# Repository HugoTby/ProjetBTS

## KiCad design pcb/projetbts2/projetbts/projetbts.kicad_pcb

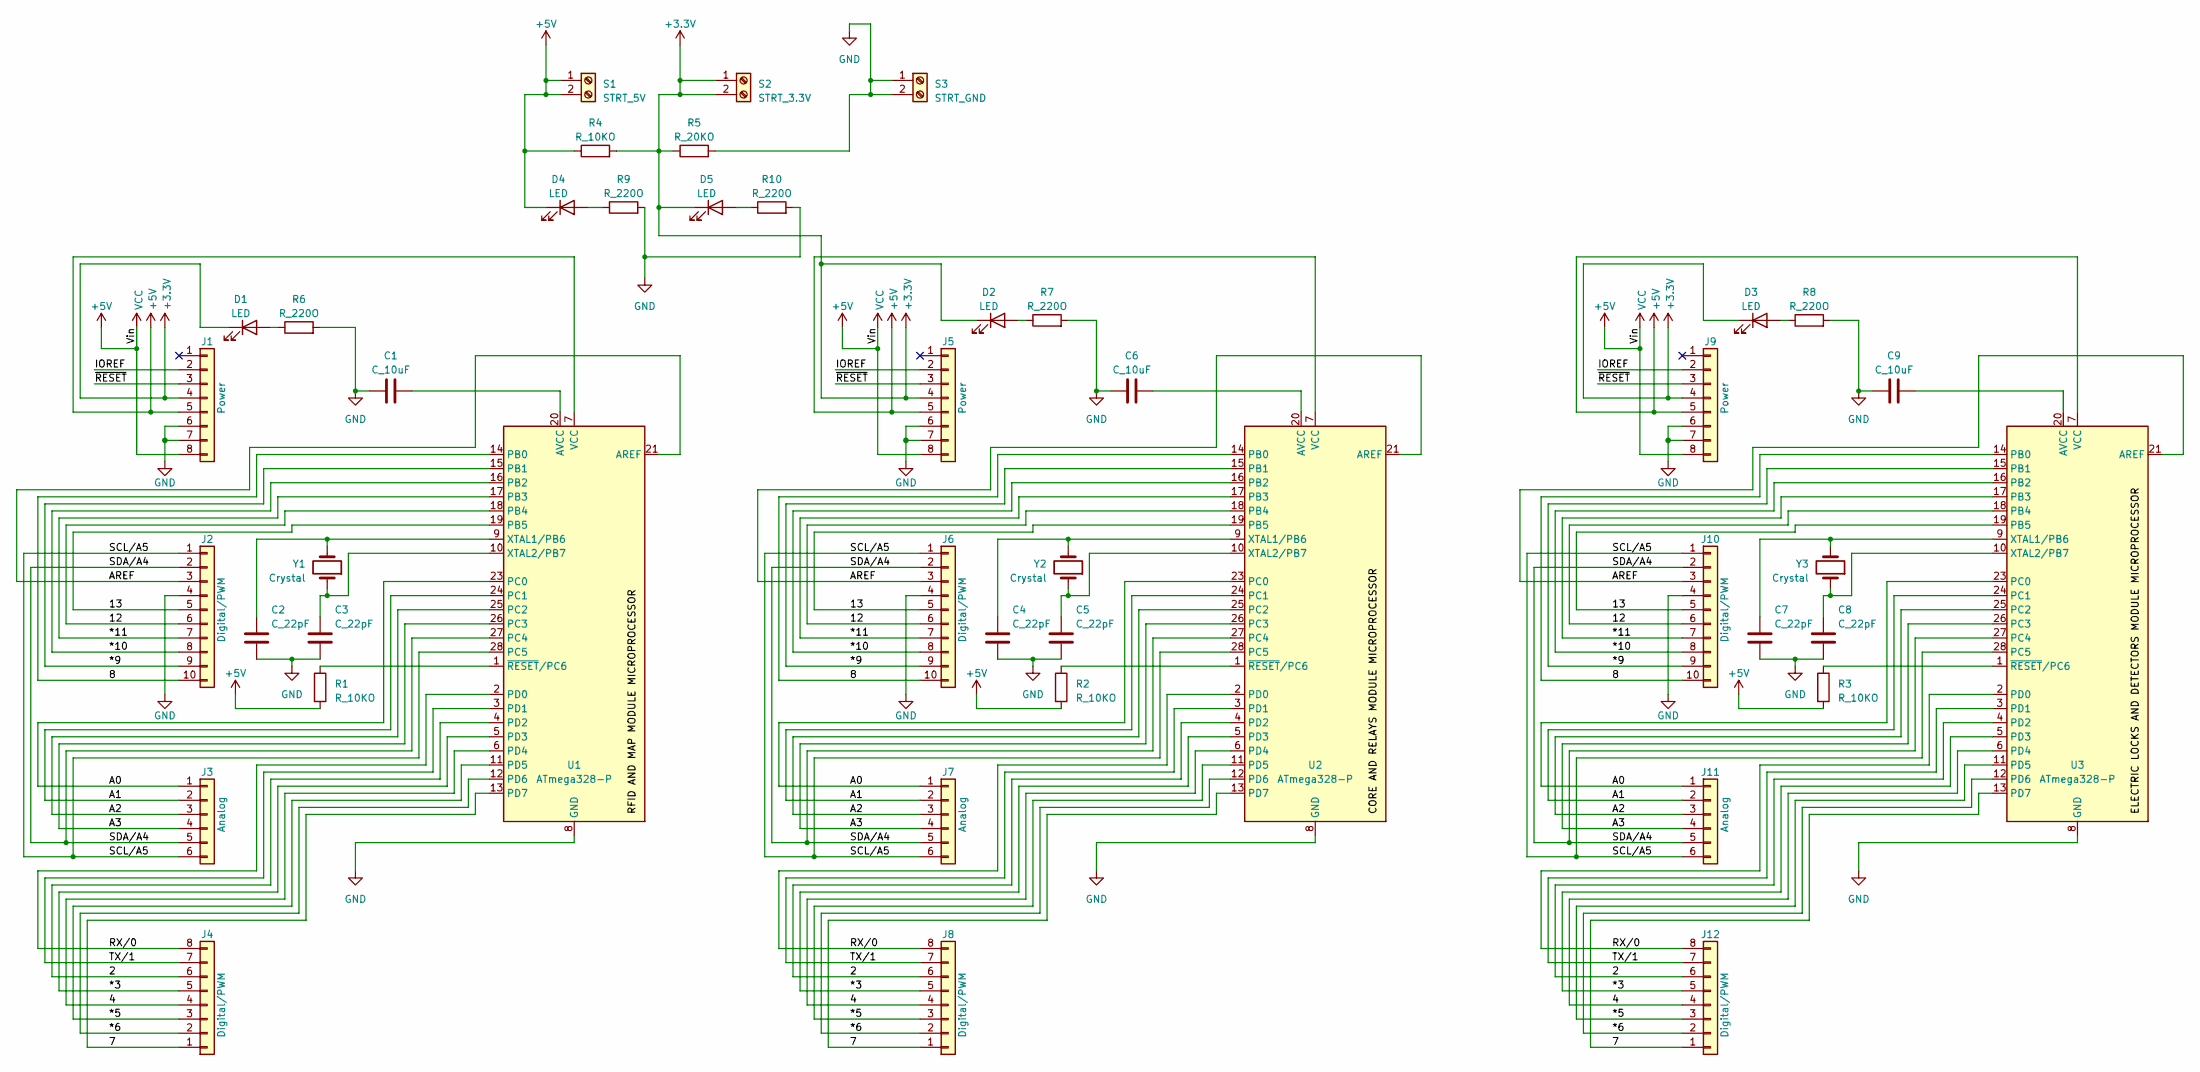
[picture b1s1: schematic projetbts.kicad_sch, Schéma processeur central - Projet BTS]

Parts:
C1, C6, C9: C_10uF; C_Disc_D7.5mm_W5.0mm_P5.00mm
C2, C3, C4, C5, C7, C8: C_22pF; C_Disc_D7.5mm_W5.0mm_P5.00mm
D1, D2, D3, D4, D5: LED; LED_D3.0mm
J1, J5, J9: Power; PinSocket_1x08_P2.54mm_Vertical
J2, J6, J10: Digital/PWM; PinSocket_1x10_P2.54mm_Vertical
J3, J7, J11: Analog; PinSocket_1x06_P2.54mm_Vertical
J4, J8, J12: Digital/PWM; PinSocket_1x08_P2.54mm_Vertical
R1, R2, R3, R4: R_10KO; R_Axial_DIN0207_L6.3mm_D2.5mm_P7.62mm_Horizontal
R5: R_20KO; R_Axial_DIN0207_L6.3mm_D2.5mm_P7.62mm_Horizontal
R6, R7, R8, R9, R10: R_220O; R_Axial_DIN0207_L6.3mm_D2.5mm_P7.62mm_Horizontal
S1: STRT_5V; TerminalBlock_bornier-2_P5.08mm
S2: STRT_3.3V; TerminalBlock_bornier-2_P5.08mm
S3: STRT_GND; TerminalBlock_bornier-2_P5.08mm
U1, U2, U3: ATmega328-P; DIP-28_W7.62mm
Y1, Y2, Y3: Crystal; Crystal_HC49-4H_Vertical

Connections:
+3.3V: D1.1 (K), D2.1 (K), D3.1 (K), D5.1 (K), J1.4, J5.4, J9.4, R4.2, R5.1, S2.1, S2.2; also elsewhere on the board
+5V: D4.1 (K), J1.5, J1.8, J5.5, J5.8, J9.5, J9.8, R1.2, R2.2, R3.2, R4.1, S1.1, S1.2, U1.7 (VCC), U2.7 (VCC), U3.7 (VCC); also elsewhere on the board
/2: J4.6, J8.6, J12.6, U1.4 (PD2), U2.4 (PD2), U3.4 (PD2)
/4: J4.4, J8.4, J12.4, U1.6 (PD4), U2.6 (PD4), U3.6 (PD4)
/7: J4.1, J8.1, J12.1, U1.13 (PD7), U2.13 (PD7), U3.13 (PD7)
/8: J2.10, J6.10, J10.10, U1.14 (PB0), U2.14 (PB0), U3.14 (PB0)
/12: J2.6, J6.6, J10.6, U1.18 (PB4), U2.18 (PB4), U3.18 (PB4)
/13: J2.5, J6.5, J10.5, U1.19 (PB5), U2.19 (PB5), U3.19 (PB5)
/*3: J4.5, J8.5, J12.5, U1.5 (PD3), U2.5 (PD3), U3.5 (PD3)
/*5: J4.3, J8.3, J12.3, U1.11 (PD5), U2.11 (PD5), U3.11 (PD5)
/*6: J4.2, J8.2, J12.2, U1.12 (PD6), U2.12 (PD6), U3.12 (PD6)
/*9: J2.9, J6.9, J10.9, U1.15 (PB1), U2.15 (PB1), U3.15 (PB1)
/*10: J2.8, J6.8, J10.8, U1.16 (PB2), U2.16 (PB2), U3.16 (PB2)
/*11: J2.7, J6.7, J10.7, U1.17 (PB3), U2.17 (PB3), U3.17 (PB3)
/A0: J3.1, J7.1, J11.1, U1.23 (PC0), U2.23 (PC0), U3.23 (PC0)
/A1: J3.2, J7.2, J11.2, U1.24 (PC1), U2.24 (PC1), U3.24 (PC1)
/A2: J3.3, J7.3, J11.3, U1.25 (PC2), U2.25 (PC2), U3.25 (PC2)
/A3: J3.4, J7.4, J11.4, U1.26 (PC3), U2.26 (PC3), U3.26 (PC3)
/AREF: J2.3, J6.3, J10.3, U1.21 (AREF), U2.21 (AREF), U3.21 (AREF)
/IOREF: J1.2, J5.2, J9.2
/RX/0: J4.8, J8.8, J12.8, U1.2 (PD0), U2.2 (PD0), U3.2 (PD0)
/SCL/A5: J2.1, J3.6, J6.1, J7.6, J10.1, J11.6, U1.28 (PC5), U2.28 (PC5), U3.28 (PC5)
/SDA/A4: J2.2, J3.5, J6.2, J7.5, J10.2, J11.5, U1.27 (PC4), U2.27 (PC4), U3.27 (PC4)
/TX/1: J4.7, J8.7, J12.7, U1.3 (PD1), U2.3 (PD1), U3.3 (PD1)
/~RESET: J1.3, J5.3, J9.3
GND: C1.1, C2.1, C3.1, C4.1, C5.1, C6.1, C7.1, C8.1, C9.1, J1.6, J1.7, J2.4, J5.6, J5.7, J6.4, J9.6, J9.7, J10.4, R5.2, R6.2, R7.2, R8.2, R9.2, R10.2, S3.1, S3.2, U1.8 (GND), U1.22 (GND), U2.8 (GND), U2.22 (GND), U3.8 (GND), U3.22 (GND); also elsewhere on the board
unnamed: D1.2 (A), R6.1
unnamed: D2.2 (A), R7.1
unnamed: D3.2 (A), R8.1
unnamed: D4.2 (A), R9.1
unnamed: D5.2 (A), R10.1
unnamed: C1.2, U1.20 (AVCC)
unnamed: C2.2, U1.9 (XTAL1/PB6), Y1.2
unnamed: C3.2, U1.10 (XTAL2/PB7), Y1.1
unnamed: R1.1, U1.1 (~RESET/PC6)
unnamed: C6.2, U2.20 (AVCC)
unnamed: C4.2, U2.9 (XTAL1/PB6), Y2.2
unnamed: C5.2, U2.10 (XTAL2/PB7), Y2.1
unnamed: R2.1, U2.1 (~RESET/PC6)
unnamed: C9.2, U3.20 (AVCC)
unnamed: C7.2, U3.9 (XTAL1/PB6), Y3.2
unnamed: C8.2, U3.10 (XTAL2/PB7), Y3.1
unnamed: R3.1, U3.1 (~RESET/PC6)

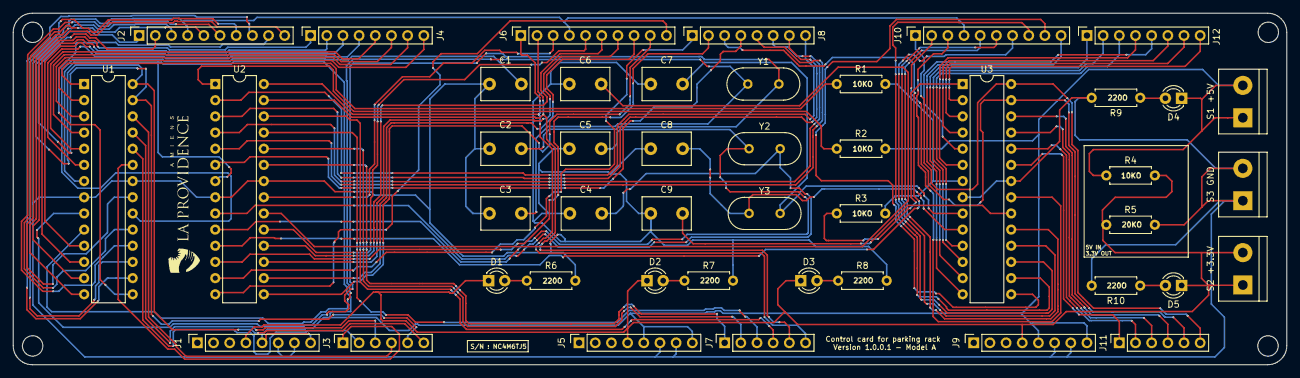
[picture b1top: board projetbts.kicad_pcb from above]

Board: 2 copper layers, 200.0 x 55.2 mm, 49 parts (0 on the bottom side), 43 nets.

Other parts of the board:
MH1, MH1#2, MH2, MH2#2: MountingHole_3.2mm
S1 +5V: STRT_5V; TerminalBlock_bornier-2_P5.08mm
S2 +3.3V: STRT_3.3V; TerminalBlock_bornier-2_P5.08mm
S3 GND: STRT_GND; TerminalBlock_bornier-2_P5.08mm

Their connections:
+3.3V: S2 +3.3V.1, S2 +3.3V.2; also elsewhere on the board
+5V: S1 +5V.1, S1 +5V.2; also elsewhere on the board
GND: S3 GND.1, S3 GND.2; also elsewhere on the board

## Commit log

2024-02-23 initialisation rfid admin
2024-02-23 création méthode insertToDatabase
2024-02-23 fonctionnement enregistrement en database pour tester
2024-03-22 module test api hassan + screens bdd
2024-03-22 integration fonctionnalité api
2024-03-25 get et set classe utilisateur
2024-03-29 module de test ajout user ok
2024-04-02 ajout diagm sequence
2024-04-18 deux premiers modules fonctionnels + revue 2
2024-04-19 ajout code arduino + librairie
2024-04-19 module de test 3 (scan badge)
2024-04-19 assemblage module scan rfid + insertUser réussi
2024-04-19 commit pre vacances
2024-05-21 implémentation de la classe modbustcp
2024-05-22 création .h de la classe inveo
2024-05-23 ajout gantt thibaut
2024-05-23 gantt modifié
2024-05-24 module de test sendAcceptSound
2024-05-28 ecoute du lecteur avec timer
2024-05-30 reparation arduino + essais rfid modbus
2024-05-31 recuperation reussie des infos de la carte dans inveo
2024-05-31 slot traitementInfos créé
2024-05-31 connexion du signal au slot
2024-05-31 bonne recup des infos mais mauvais conversion des donnees
2024-06-03 ajout test4 img + conditions inveo ameliorées
2024-06-03 modif commentaires
2024-06-03 ajout screens/fonction box dispo
2024-06-03 passage des boxDispo en int plutot que string
2024-06-03 ouverture communication serie + envoi commande reussis
2024-06-06 reparation ouverture port
